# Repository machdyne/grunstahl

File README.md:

# Grünstahl

Grünstahl is a USB-C device that provides access to 2 KB of Ferroelectric RAM over USB HID.

This repo contains schematics, firmware, software, documentation and a 3D printable case.

See the [product page](https://machdyne.com/product/grunstahl) for more information.

## Software

The 'hidxfer' utility or the WebHID-based hex/text editor can be used to access the data. There is also a native Android version of the hex/text editor.

## Building hidxfer (Linux)

```bash
cd sw
sudo apt install libhidapi-dev
make
```

On Linux you may need a udev rule to access the device without root.
Create /etc/udev/rules.d/99-grunstahl.rules:

  SUBSYSTEM=="hidraw", ATTRS{idVendor}=="1209", ATTRS{idProduct}=="d003", MODE="0666"

Then: sudo udevadm control --reload-rules && sudo udevadm trigger

## Usage

```bash
# Ping the device
./hidxfer --ping

# Read the entire 2 KB of FRAM to a file
./hidxfer -r backup.bin --bytes 2048

# Read 512 bytes starting at offset 1024
./hidxfer -r partial.bin --offset 1024 --bytes 512

# Write a file to FRAM starting at offset 0
./hidxfer -w data.txt

# Write a file to FRAM starting at offset 512
./hidxfer -w data.dat --offset 512
```

## Building the firmware

Updating the firmware requires a WCH-LinkE or other CH32V003 programmer. The SWIO header is labeled on the board.

```bash
cd fw
make        # builds grunstahl.bin
make flash  # flashes via WCH-LinkE (minichlink)
```

Requires: RISC-V GCC toolchain (riscv-none-embed-gcc or riscv32-unknown-elf-gcc).

## Protocol

```
255-byte HID feature report, report ID 0xaa.

Request (host to device):

  [0]    0xaa   magic
  [1]    0x00   request marker
  [2]    cmd    0x00=PING  0x01=READ  0x02=WRITE
  [3]    addr_lo  FRAM address low byte
  [4]    addr_hi  FRAM address high byte
  [5]    len    payload byte count (max 248)
  [6..]  data   write payload (WRITE only)

Response (device to host, polled until [1] == 0x01):

  [0]    0xaa   magic
  [1]    0x01   response marker
  [2]    status 0x01=ok  0x00=error
  [3..]  data   read payload (READ only)

Transfers larger than 248 bytes are automatically chunked by hidxfer.
```

## LLM-generated code

To the extent that there is LLM-generated code in this repo, it should be space indented. Any space indented code should be carefully audited and then converted to tabs (eventually).

## License

The contents of this repo are released under the [Lone Dynamics Open License](LICENSE.md) with the following exceptions:

  * The ch32fun library is MIT licensed.
  * The hidapi library is BSD licensed.

Note: You can use these designs for commercial purposes but we ask that instead of producing exact clones, that you either replace our trademarks and logos with your own or add your own next to ours.

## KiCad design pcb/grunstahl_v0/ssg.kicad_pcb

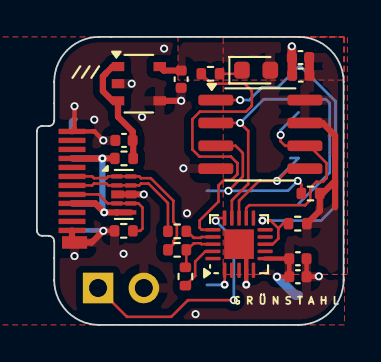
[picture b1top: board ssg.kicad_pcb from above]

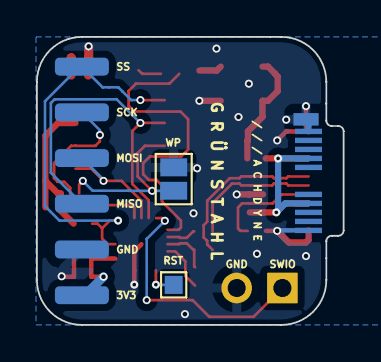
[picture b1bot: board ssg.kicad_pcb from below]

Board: 2 copper layers, 17.0 x 16.0 mm, 24 parts (3 on the bottom side), 19 nets.

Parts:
C1, C3: 100nF; C_0402_1005Metric
C2: 10uF; C_0402_1005Metric
C4, C5, C6: 1uF; C_0402_1005Metric
D1: LEDG; LED_0603_1608Metric
FB1: Ferrite_Bead_Small; R_0402_1005Metric
J1: Conn_01x06; LD-SMD-FEMALE-1x06
J2: Conn_01x02_Pin; PinHeader_1x02_P2.54mm_Vertical
JP1: Jumper_2_Open; SolderJumper-2_P1.3mm_Open_Pad1.0x1.5mm
P1: USB_C_Plug_USB2.0; USB_C_Plug_SHOUHAN_GTJB-040
R1: 1K5; R_0402_1005Metric
R2, R3: 33R; R_0402_1005Metric
R4, R6: 10K; R_0402_1005Metric
R8: 1K; R_0402_1005Metric
R9: 5K1; R_0402_1005Metric
TP1: TestPoint; TestPoint_Pad_1.0x1.0mm
U1: MB85RS16; SOIC-8_3.9x4.9mm_P1.27mm
U2: CH32V003FxUx; QFN-20-1EP_3x3mm_P0.4mm_EP1.65x1.65mm
U3: NCP115; TSOP-5_1.65x3.05mm_P0.95mm
U5: ESD224DQA; Diodes_UDFN-10_1.0x2.5mm_P0.5mm

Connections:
/LED: R8.2, U2.16 (PD2)
/PWR3V3: C1.1, C2.1, C3.1, C5.1, C6.1, D1.2 (A), J1.6, R4.2, R6.2, U1.7 (~HOLD), U1.8 (VDD), U2.6 (VDD), U3.5 (OUT)
/PWR5V0: C4.1, FB1.1, U3.1 (IN), U3.3 (EN)
/RAM_MISO: J1.4, U1.2 (SO), U2.14 (PC7)
/RAM_MOSI: J1.3, U1.5 (SI), U2.13 (PC6)
/RAM_SCK: J1.2, U1.6 (SCK), U2.12 (PC5)
/RAM_SS: J1.1, R4.1, U1.1 (~CS), U2.8 (PC1)
/RESET: TP1.1, U2.1 (PD7)
/SWIO: J2.1, U2.15 (PD1)
/USBC_CC: P1.A5 (CC), R9.2, U5.4, U5.7
/USBC_DN: P1.A7 (D-), R2.1, U5.1, U5.10
/USBC_DP: P1.A6 (D+), R3.1, U5.2, U5.9
/USB_DN: R1.2, R2.2, U2.18 (PD4)
/USB_DN_PU: R1.1, U2.19 (PD5)
/USB_DP: R3.2, U2.17 (PD3)
/VBUS: FB1.2, P1.A4 (VBUS), P1.A9 (VBUS), P1.B4 (VBUS), P1.B9 (VBUS), U5.5, U5.6
/WP: JP1.1 (A), R6.1, U1.3 (~WP)
GND: C1.2, C2.2, C3.2, C4.2, C5.2, C6.2, J1.5, J2.2, JP1.2 (B), P1.A1 (GND), P1.A12 (GND), P1.B1 (GND), P1.B12 (GND), P1.S1 (SHIELD), R9.1, U1.4 (GND), U2.4 (VSS), U2.21 (VSS), U3.2 (GND), U3.4 (GND2), U5.3 (VSS), U5.8 (VSS)
unnamed: D1.1 (K), R8.1

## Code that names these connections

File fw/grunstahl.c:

/*
 * Grünstahl Firmware
 *
 * CH32V003 USB HID device providing read/write access to 2 KB of SPI F-RAM.
 * Based on Einszeit by Lone Dynamics Corporation / CNLohr.
 *
 * Protocol (255-byte HID feature report, report ID 0xaa):
 *
 *   Request  (host → device):
 *     [0]     0xaa        magic
 *     [1]     0x00        direction (request)
 *     [2]     cmd         GS_CMD_*
 *     [3..4]  addr_lo,hi  16-bit FRAM address (little-endian)
 *     [5]     len         payload length in bytes (max 248)
 *     [6..]   data        payload (write only)
 *
 *   Response (device → host):
 *     [0]     0xaa        magic
 *     [1]     0x01        direction (response)
 *     [2]     status      0x01 = ok, 0x00 = error
 *     [3..]   data        payload (read only)
 *
 * Commands:
 *   GS_CMD_PING   0x00   — returns ok, no data
 *   GS_CMD_READ   0x01   — read len bytes from addr → response[3..]
 *   GS_CMD_WRITE  0x02   — write len bytes at addr from request[6..]
 *
 * Pinout:
 *   PC1  FRAM_SS   (SPI chip select, active-low)
 *   PC5  FRAM_SCK  (SPI clock)
 *   PC6  FRAM_MOSI (SPI data out)
 *   PC7  FRAM_MISO (SPI data in)
 *   PD2  LED       (activity, active-high)
 *   PD3  USB D+
 *   PD4  USB D-    (1.5k pull-up via PD5 → Low-Speed)
 *   PD5  USB PU
 */

#include <stdio.h>
#include <string.h>
#include <stdint.h>
#include "rv003usb.h"
#include "ch32fun.h"

/* ── Protocol ───────────────────────────────────────────────────────────── */

#define GS_CMD_PING   0x00
#define GS_CMD_READ   0x01
#define GS_CMD_WRITE  0x02

#define GS_MAX_PAYLOAD 248   /* 255 - 7 header bytes */
#define FRAM_SIZE      2048

/* ── Pins ───────────────────────────────────────────────────────────────── */

#define FRAM_SS_PIN   1   /* PC1 */
#define FRAM_SCK_PIN  5   /* PC5 */
#define FRAM_MOSI_PIN 6   /* PC6 */
#define FRAM_MISO_PIN 7   /* PC7 */
#define LED_PIN       2   /* PD2 */

/* ── SPI helpers ────────────────────────────────────────────────────────── */

static inline void ss_low(void)   { GPIOC->BSHR = (1u << (16 + FRAM_SS_PIN)); }
static inline void ss_high(void)  { GPIOC->BSHR = (1u << FRAM_SS_PIN); }
static inline void sck_low(void)  { GPIOC->BSHR = (1u << (16 + FRAM_SCK_PIN)); }
static inline void sck_high(void) { GPIOC->BSHR = (1u << FRAM_SCK_PIN); }
static inline void mosi_set(int b) {
    if (b) GPIOC->BSHR = (1u << FRAM_MOSI_PIN);
    else   GPIOC->BSHR = (1u << (16 + FRAM_MOSI_PIN));
}
static inline int miso_read(void) { return (GPIOC->INDR >> FRAM_MISO_PIN) & 1; }

static uint8_t spi_xfer(uint8_t tx)
{
    uint8_t rx = 0;
    for (int i = 7; i >= 0; i--) {
        mosi_set((tx >> i) & 1);
        sck_high();
        rx = (uint8_t)((rx << 1) | miso_read());
        sck_low();
    }
    return rx;
}

/* ── FRAM driver ────────────────────────────────────────────────────────── */

#define FRAM_OP_WREN  0x06
#define FRAM_OP_READ  0x03
#define FRAM_OP_WRITE 0x02

static void fram_init(void)
{
    RCC->APB2PCENR |= RCC_APB2Periph_GPIOC;

    uint32_t crl = GPIOC->CFGLR;
    /* PC1 SS   output PP 10MHz (bits  7:4) */
    crl &= ~(0xFu <<  4); crl |= (0x1u <<  4);
    /* PC5 SCK  output PP 10MHz (bits 23:20) */
    crl &= ~(0xFu << 20); crl |= (0x1u << 20);
    /* PC6 MOSI output PP 10MHz (bits 27:24) */
    crl &= ~(0xFu << 24); crl |= (0x1u << 24);
    /* PC7 MISO input floating (bits 31:28) */
    crl &= ~(0xFu << 28); crl |= (0x4u << 28);
    GPIOC->CFGLR = crl;

    ss_high();
    sck_low();
}

static void fram_read(uint16_t addr, uint8_t *buf, uint16_t len)
{
    ss_low();
    spi_xfer(FRAM_OP_READ);
    spi_xfer((uint8_t)(addr >> 8));
    spi_xfer((uint8_t)(addr & 0xFF));
    for (uint16_t i = 0; i < len; i++)
        buf[i] = spi_xfer(0x00);
    ss_high();
}

static void fram_write(uint16_t addr, const uint8_t *buf, uint16_t len)
{
    /* WREN — latch clears after each /CS rising edge */
    ss_low(); spi_xfer(FRAM_OP_WREN); ss_high();

    ss_low();
    spi_xfer(FRAM_OP_WRITE);
    spi_xfer((uint8_t)(addr >> 8));
    spi_xfer((uint8_t)(addr & 0xFF));
    for (uint16_t i = 0; i < len; i++)
        spi_xfer(buf[i]);
    ss_high();
}

/* ── LED ────────────────────────────────────────────────────────────────── */

static void led_init(void)
{
    RCC->APB2PCENR |= RCC_APB2Periph_GPIOD;
    GPIOD->CFGLR &= ~(0xFu << (4 * LED_PIN));
    GPIOD->CFGLR |=  (GPIO_Speed_10MHz | GPIO_CNF_OUT_PP) << (4 * LED_PIN);
    GPIOD->BSHR = (1u << (16 + LED_PIN)); /* off */
}

static inline void led_on(void)  { GPIOD->BSHR = (1u << LED_PIN); }
static inline void led_off(void) { GPIOD->BSHR = (1u << (16 + LED_PIN)); }

/* ── Shared HID scratch buffer (same pattern as Einszeit) ───────────────── */

uint8_t scratch[255];
volatile uint8_t start = 0;

/* ── Command handler ────────────────────────────────────────────────────── */

static void handle_command(void)
{
    uint8_t cmd    = scratch[2];
    uint16_t addr  = (uint16_t)(scratch[3] | (scratch[4] << 8));
    uint8_t  len   = scratch[5];

    /* Clamp len to safe maximum and FRAM bounds */
    if (len > GS_MAX_PAYLOAD) len = GS_MAX_PAYLOAD;
    if ((uint32_t)addr + len > FRAM_SIZE) {
        scratch[2] = 0x00; /* error */
        return;
    }

    led_on();

    switch (cmd) {

        case GS_CMD_PING:
            scratch[2] = 0x01;
            break;

        case GS_CMD_READ:
            fram_read(addr, &scratch[3], len);
            scratch[2] = 0x01;
            break;

        case GS_CMD_WRITE:
            fram_write(addr, &scratch[6], len);
            scratch[2] = 0x01;
            break;

        default:
            scratch[2] = 0x00; /* unknown command */
            break;
    }

    led_off();
}

/* ── Main ───────────────────────────────────────────────────────────────── */

int main(void)
{
    SystemInit();
    Delay_Ms(1); /* ensure USB re-enumeration after reset */

    led_init();
    fram_init();

    usb_setup();

    while (1) {
#if RV003USB_EVENT_DEBUGGING
        uint32_t *ue = GetUEvent();
        if (ue) printf("%lu %lx %lx %lx\n", ue[0], ue[1], ue[2], ue[3]);
#endif
        if (start && scratch[0] == 0xaa && scratch[1] == 0x00) {
            handle_command();
            scratch[1] = 0x01; /* mark as response */
            start = 0;
        }
    }
}

/* ── rv003usb HID callbacks (identical pattern to Einszeit) ─────────────── */

void usb_handle_user_in_request(struct usb_endpoint *e, uint8_t *scratchpad,
                                int endp, uint32_t sendtok,
                                struct rv003usb_internal *ist)
{
    if (endp) usb_send_empty(sendtok);
}

void usb_handle_user_data(struct usb_endpoint *e, int current_endpoint,
                          uint8_t *data, int len,
                          struct rv003usb_internal *ist)
{
    int offset = e->count << 3;
    int torx   = e->max_len - offset;
    if (torx > len) torx = len;
    if (torx > 0) {
        memcpy(scratch + offset, data, torx);
        e->count++;
        if ((e->count << 3) >= e->max_len)
            start = e->max_len;
    }
}

void usb_handle_hid_get_report_start(struct usb_endpoint *e, int reqLen,
                                     uint32_t lValueLSBIndexMSB)
{
    if (reqLen > (int)sizeof(scratch)) reqLen = sizeof(scratch);
    e->opaque  = scratch;
    e->max_len = reqLen;
}

void usb_handle_hid_set_report_start(struct usb_endpoint *e, int reqLen,
                                     uint32_t lValueLSBIndexMSB)
{
    if (reqLen > (int)sizeof(scratch)) reqLen = sizeof(scratch);
    e->max_len = reqLen;
}

void usb_handle_other_control_message(struct usb_endpoint *e,
                                      struct usb_urb *s,
                                      struct rv003usb_internal *ist)
{
    LogUEvent(SysTick->CNT, s->wRequestTypeLSBRequestMSB,
              s->lValueLSBIndexMSB, s->wLength);
}

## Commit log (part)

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2026-06-20 add render
2026-06-20 add android app
2026-06-20 add enclosure
2026-06-23 add kicad files
2026-06-26 update pid
